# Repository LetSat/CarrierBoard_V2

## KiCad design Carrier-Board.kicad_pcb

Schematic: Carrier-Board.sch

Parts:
C1, C3: 10uF; C_0805_2012Metric
C2: 22uF; C_0805_2012Metric
C4: 22uF; C_0603_1608Metric
C5, C6, C10, C27, C28, C29: .1uF; C_0603_1608Metric
C7: 47nF; C_0603_1608Metric
C8, C11, C12: .33uF; C_0603_1608Metric
C9: 4.7uF; C_0603_1608Metric
D1: PESD12VL2BT,215; D_SOT-23_NKA
D2, D3, D6, D7, D8: LED; D_0805_2012Metric
D5: D_Zener 9V; D_SOD-323
G1: LOGO; LetSat_Logo_440
J1: CONN_3-6318491-6; ComExpressMini10
J2: Conn_01x0; Barrel_Jack_CUI_PJ-036AH-SMT
J3, J5: Conn_02x26_Odd_Even; ESQ-126-XX-X-D
J4: SI-51009-F; Manufacturer_Part_Number SI-51009-F
J6: Conn_01x03_Male; Pin_Header_Angled_1x03_Pitch2.54mm
J7: Conn_01x03_Male; TestPoint_Pad_D3.0mm
J8: Conn_01x06_Male; Pin_Header_Angled_1x06_Pitch2.54mm
J9: Conn_02x04_Odd_Even; Pin_Header_Angled_2x04_Pitch2.54mm
J10: Conn_02x03_Odd_Even; Pin_Header_Angled_2x03_Pitch2.54mm
J11: USB_B_Micro; USB_Micro-B_Molex-105017-0001
R1, R5: 160k; R_0603_1608Metric
R2: 30.1k; R_0603_1608Metric
R3, R7: 100k; R_0603_1608Metric
R4: 63.4k; R_0603_1608Metric
R6: 51k; R_0603_1608Metric
R8: 56k; R_0603_1608Metric
R9, R16, R23: 330; R_0603_1608Metric
R10, R11, R12, R13, R14: 10K; R_0603_1608Metric
R15: 4.7K; R_0603_1608Metric
R17, R18: 200; R_0603_1608Metric
R24: 180; R_0603_1608Metric
R25: 1k; R_0603_1608Metric
R32: 0; R_0603_1608Metric
SW1, SW2, SW3: SW_Push; SW_SPST_B3U-1000P
U1, U2: MPM3620; QFN-20
U3: MAX3221; SSOP-16_5.3x6.2mm_Pitch0.65mm
U4: FT232RQ; QFN50P500X500X100-33N
U9: MSATA-Socket; mpcie-socket

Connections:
+3.3V: C4.1, C27.1, C28.1, C29.1, D7.2 (A), J10.2, R5.1, U2.7, U2.8, U2.9, U9.2, U9.24, U9.39, U9.41, U9.52
GBE0_CTREF(GND): C1.2, C2.2, C3.2, C4.2, C5.2, C6.2, C9.2, C10.2, C11.2, C12.2, C27.2, C28.2, C29.2, D1.3, J1.1, J1.11, J1.14, J1.21, J1.31, J1.41, J1.51, J1.57, J1.60, J1.66, J1.70, J1.80, J1.90, J1.100, J1.110, J1.111, J1.121, J1.131, J1.141, J1.151, J1.161, J1.170, J1.180, J1.190, J1.200, J1.210, J1.220, J2.2, J4.1, J4.6, J4.17, J4.18, J6.1, J8.6, J10.6, J11.5, J11.6, R9.1, R10.1, R16.1, R23.1, R24.1, R25.1, R32.2, SW1.1, SW2.1, SW3.1, U1.12, U1.13, U1.14, U2.12, U2.13, U2.14, U3.1, U3.12, U3.14, U4.4, U4.17, U4.20, U4.24, U4.26, U4.33, U9.4, U9.9, U9.15, U9.18, U9.21, U9.26, U9.27, U9.29, U9.34, U9.35, U9.37, U9.40, U9.50
GBE0_LINK100#: J1.4, J4.16
GBE0_LINK1000#: J1.5, J4.13
GBE0_MDI0+: J1.13, J4.2
GBE0_MDI0-: J1.12, J4.3
GBE0_MDI1+: J1.10, J4.4
GBE0_MDI1-: J1.9, J4.5
GBE0_MDI2+: J1.7, J4.7
GBE0_MDI2-: J1.6, J4.8
GBE0_MDI3+: J1.3, J4.9
GBE0_MDI3-: J1.2, J4.10
GNDA: R2.2, R4.2, R6.2, R8.2, U1.3, U2.3
GPI0: J1.54, J9.1
GPI1: J1.63, J9.3
GPI2: J1.67, J9.5
GPI3: J1.85, J9.7
GPO0: J1.93, J9.2
GPO1: J1.164, J9.4
GPO2: J1.167, J9.6
GPO3: J1.173, J9.8
I2C_CK: J1.143, J6.3
I2C_DAT: J1.144, J6.2
unnamed: C7.1, U3.2
unnamed: C7.2, U3.4
unnamed: C8.1, U3.5
unnamed: C8.2, U3.6
unnamed: C10.1, U4.16
unnamed: C11.1, U3.3
unnamed: C12.1, U3.7
unnamed: D1.1, J11.2, U4.15
unnamed: D1.2, J11.3, U4.14
unnamed: D2.1, R17.1
unnamed: D3.1, R18.1
unnamed: D5.2 (A), D6.2 (A)
unnamed: D6.1 (K), R24.2
unnamed: D7.1 (K), R23.2
unnamed: D8.1 (K), R25.2
unnamed: J4.14, R16.2
unnamed: J4.15, R9.2
unnamed: J11.1, R15.1
unnamed: R1.2, R2.1, U1.1
unnamed: R3.2, U1.17
unnamed: R4.1, U1.18
unnamed: R5.2, R6.1, U2.1
unnamed: R7.2, U2.17
unnamed: R8.1, U2.18
unnamed: R14.2, U4.10
unnamed: R17.2, U4.22
unnamed: R18.2, U4.21
unnamed: R32.1, U9.51
PWRBTNn: J1.122, J8.5, R11.1, SW1.2
PWR_OK: J1.134, J8.2
RXD: U3.9, U4.2
Reset#: R10.2, R15.2, U4.18
SATA0_RX+: J1.19, U9.23
SATA0_RX-: J1.20, U9.25
SATA0_TX+: J1.16, U9.33
SATA0_TX-: J1.17, U9.31
SATA_ACTn: J1.28, U9.49
SLEEPn: J1.213, J8.1
SPI_CLK: J1.94, J10.3
SPI_CS#: J1.97, J10.5
SPI_MISO: J1.92, J10.1
SPI_MOSI: J1.95, J10.4
SYS_RESETn: J1.159, J8.4, R12.2, SW2.2
TXD: U3.11, U4.30
WAKE1n: J1.177, J8.3, R13.2, SW3.2
mCOM_5V_SBY: C2.1, C5.1, C6.1, C9.1, D2.2, D3.2, D8.2 (A), J1.194, J1.195, J1.196, J1.197, R1.1, R11.2, R12.1, R13.1, R14.1, U1.7, U1.8, U1.9, U3.15, U3.16, U4.1, U4.19
mCOM_12V: C1.1, C3.1, D5.1 (K), J1.104, J1.105, J1.106, J1.107, J1.108, J1.109, J1.214, J1.215, J1.216, J1.217, J1.218, J1.219, J2.1, R3.1, R7.1, U1.16, U2.16
mCOM_RX: J1.99, U3.13
mCOM_TX: J1.98, U3.8

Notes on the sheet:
Break out
LED Indicators
3V3
12V
5V SBY
Voltage Supply
LetSat-1 Carrier Prototype
Spring 2018
Sata Connector
mCOMTK1
I2C
Rs232
SPI
GPIO
MISC SHIT
PC104
Pixie Wranglers: Prabodh Jhaveri Chandler Griscom
polarized +
polarized -
Ethernet
USB to RS232

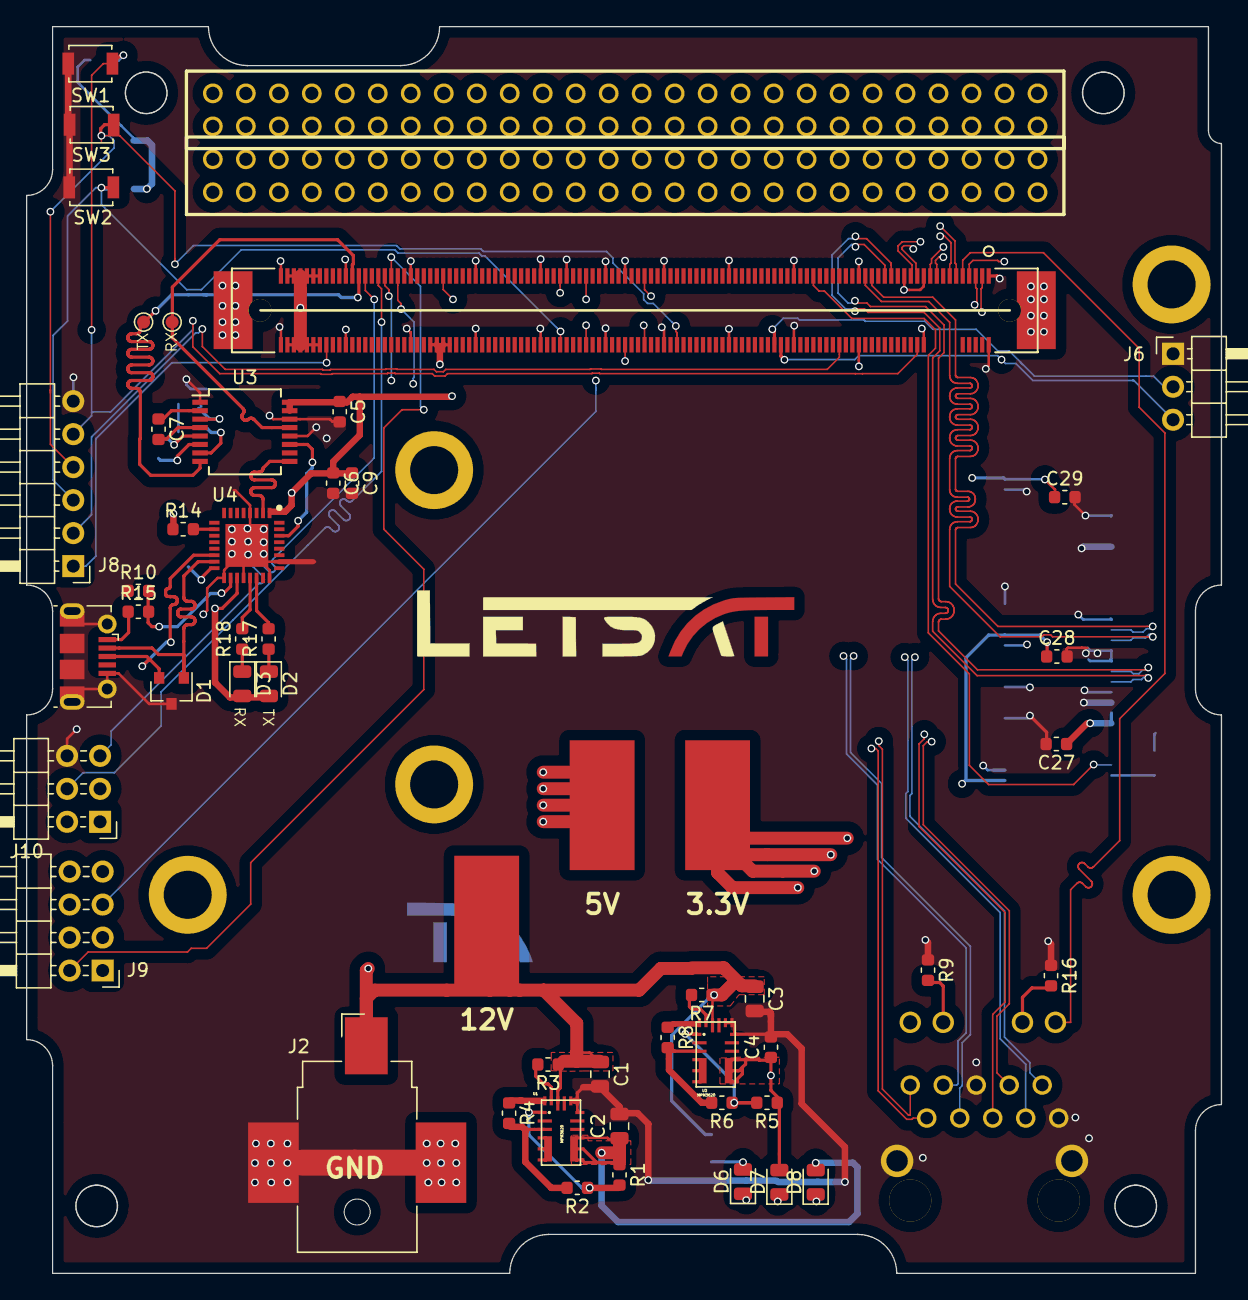
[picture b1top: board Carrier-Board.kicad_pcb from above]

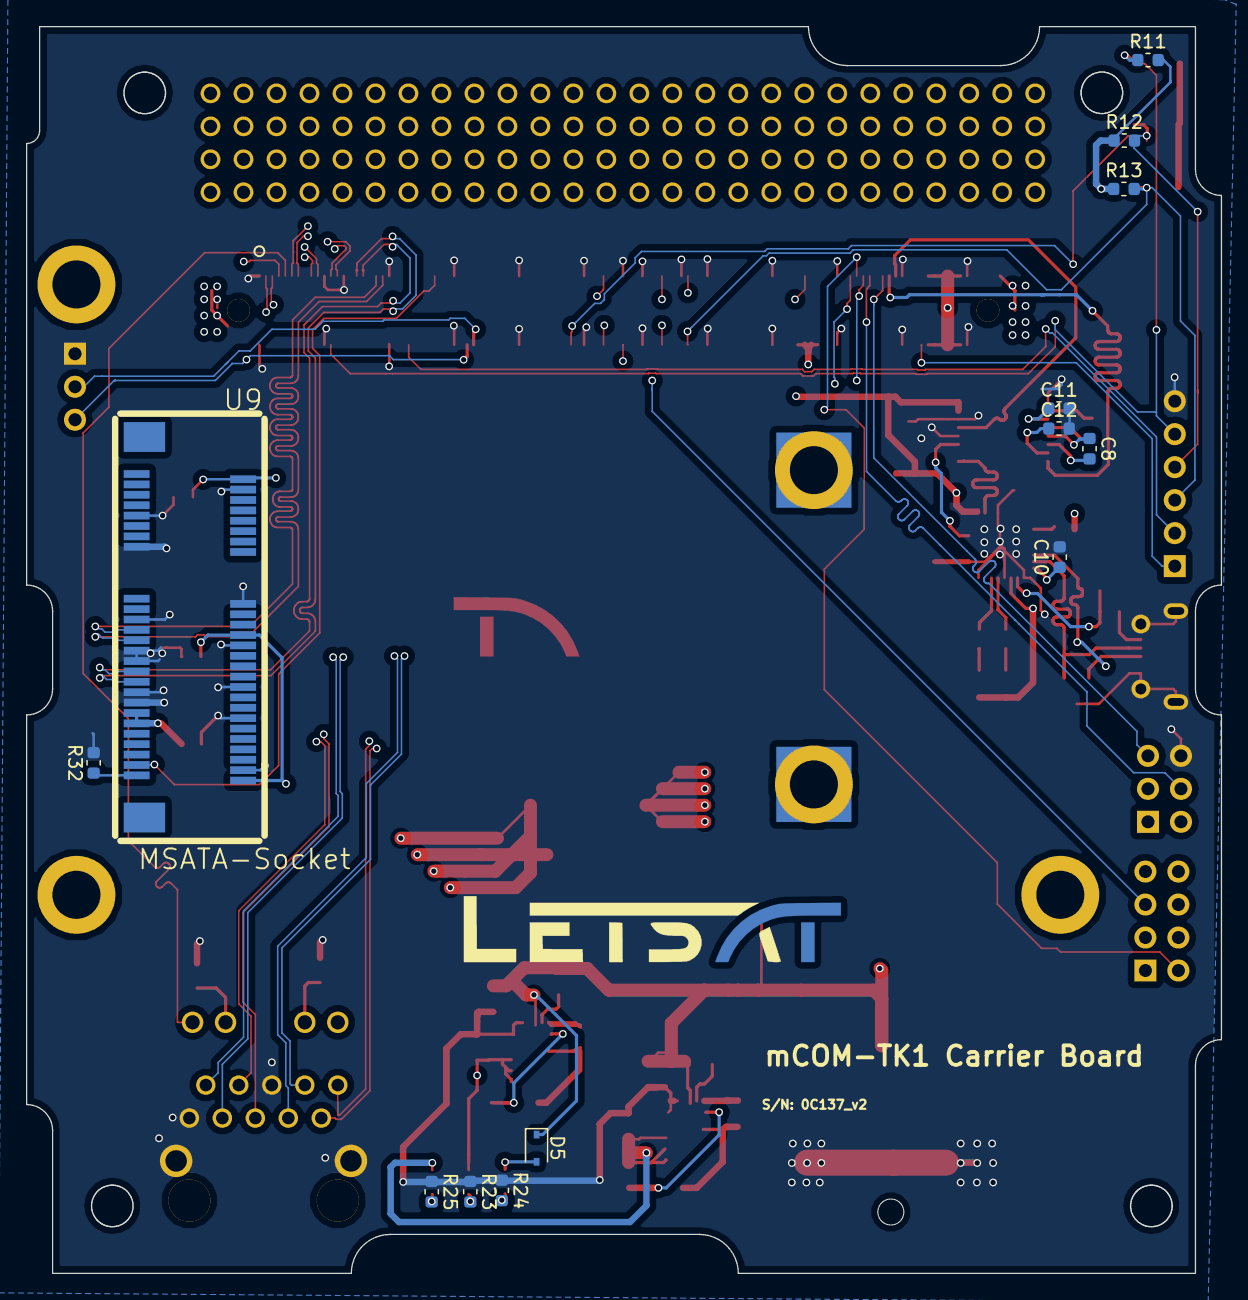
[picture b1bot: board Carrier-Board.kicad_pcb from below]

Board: 4 copper layers, 92.0 x 96.0 mm, 69 parts (14 on the bottom side), 72 nets.

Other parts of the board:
G1#2: LOGO; LetSat_Logo_440
m1, m1#2, m1#3, m1#4, m2: MountingHole_2.7mm_M2.5_Pad

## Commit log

2018-09-14 Master Commit
2018-09-19 rs232
2018-09-19 lib stuff'
2018-09-19 added usb
2018-09-21 Finished Schematic for RS232 to USB
2018-09-22 Finished USB>rs232
    Verify needed
2018-09-22 changed serial number
2018-09-23 Add gitignore
2018-09-23 Remove some stuff
2018-09-23 Fix broken libraries
2018-09-23 Change footprint sizes
2018-09-23 CLEAN UP
2018-09-25 added 3d models
2018-09-25 edited image

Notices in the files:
parts and their libraries:
Copyright 2016 Accelerated Designs. All rights reserved.
